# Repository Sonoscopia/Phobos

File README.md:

# PHOBOS
Code and instructional content.
Homepage is [here](https://sonoscopia.pt/en/works/phobos/) 

## Description
Phobos is a set of small robots and automatic music generation devices that form a Dysfunctional Robotic Orchestra, an orchestra with strange instruments with defects, genetic mutations and erratic behaviors.

Phobos represents a critique of the technological overlapping over human thought, the function of labor and modern forms of slavery, as well as an historical retrospective of the various attempts of human liberation through machines, its technological utopias, the advances and retreats of freedoms. Its name comes from Greek mythology, where Phobos is the incarnation of fear, and is also the name of the largest moon of Mars, doomed to disappear due to the proximity of its orbit to the planet. 

## Credits
- Conception and artistic direction: Gustavo Costa 
- New instruments by: Henrique Fernandes, Gustavo Costa, Alberto Lopes
- Guest musicians and instrument builders: Thierry Madiot, Vincent Martial and Hanna Hartman
- Programming and robotics: Tiago Ângelo and João Menezes
- Composition: Carlos Guedes, Rui Dias and José Alberto Gomes
- Cenography: Igor Gandra (Teatro de Ferro)
- Video: Miguel C. Tavares
- Executive production: Patrícia Caveiro
- Production: Sonoscopia
- Technical assistance: Digitópia
- Logistic support: Teatro de Ferro
- Project funded by Republica Portuguesa / Cultura and DGArtes
- Partners: GNRation, NYU Abu Dhabi, CCVF, Centro Cultural de Ílhavo and Festival Bons Sons

## LICENSE
[![CC BY-NC 4.0][cc-by-nc-shield]][cc-by-nc]

This work is licensed under a
[Creative Commons Attribution-NonCommercial 4.0 International License][cc-by-nc].

[![CC BY-NC 4.0][cc-by-nc-image]][cc-by-nc]

[cc-by-nc]: https://creativecommons.org/licenses/by-nc/4.0/
[cc-by-nc-image]: https://licensebuttons.net/l/by-nc/4.0/88x31.png
[cc-by-nc-shield]: https://img.shields.io/badge/License-CC%20BY--NC%204.0-lightgrey.svg

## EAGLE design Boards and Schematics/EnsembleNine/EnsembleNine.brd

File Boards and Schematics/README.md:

# IMPORTANT NOTICE
These boards were designed to be etched and drilled by CNC at FEUP (Faculty of Engineering - University of Porto) in 2015. 

The boards might need some revision for modern print (ex: JLCPCB or PCBWAY)!!

If you want to make one for yourself I would advise making EnsembleTwo (check schematics to see which one better fits your needs...)

The Ensemble boards used RJ45 connectors, packing 4 signals in one cable. To use independent outputs the InstrumentHubs have a RJ45 input connector and separate output DC (5.5x2.1mm) connectors.

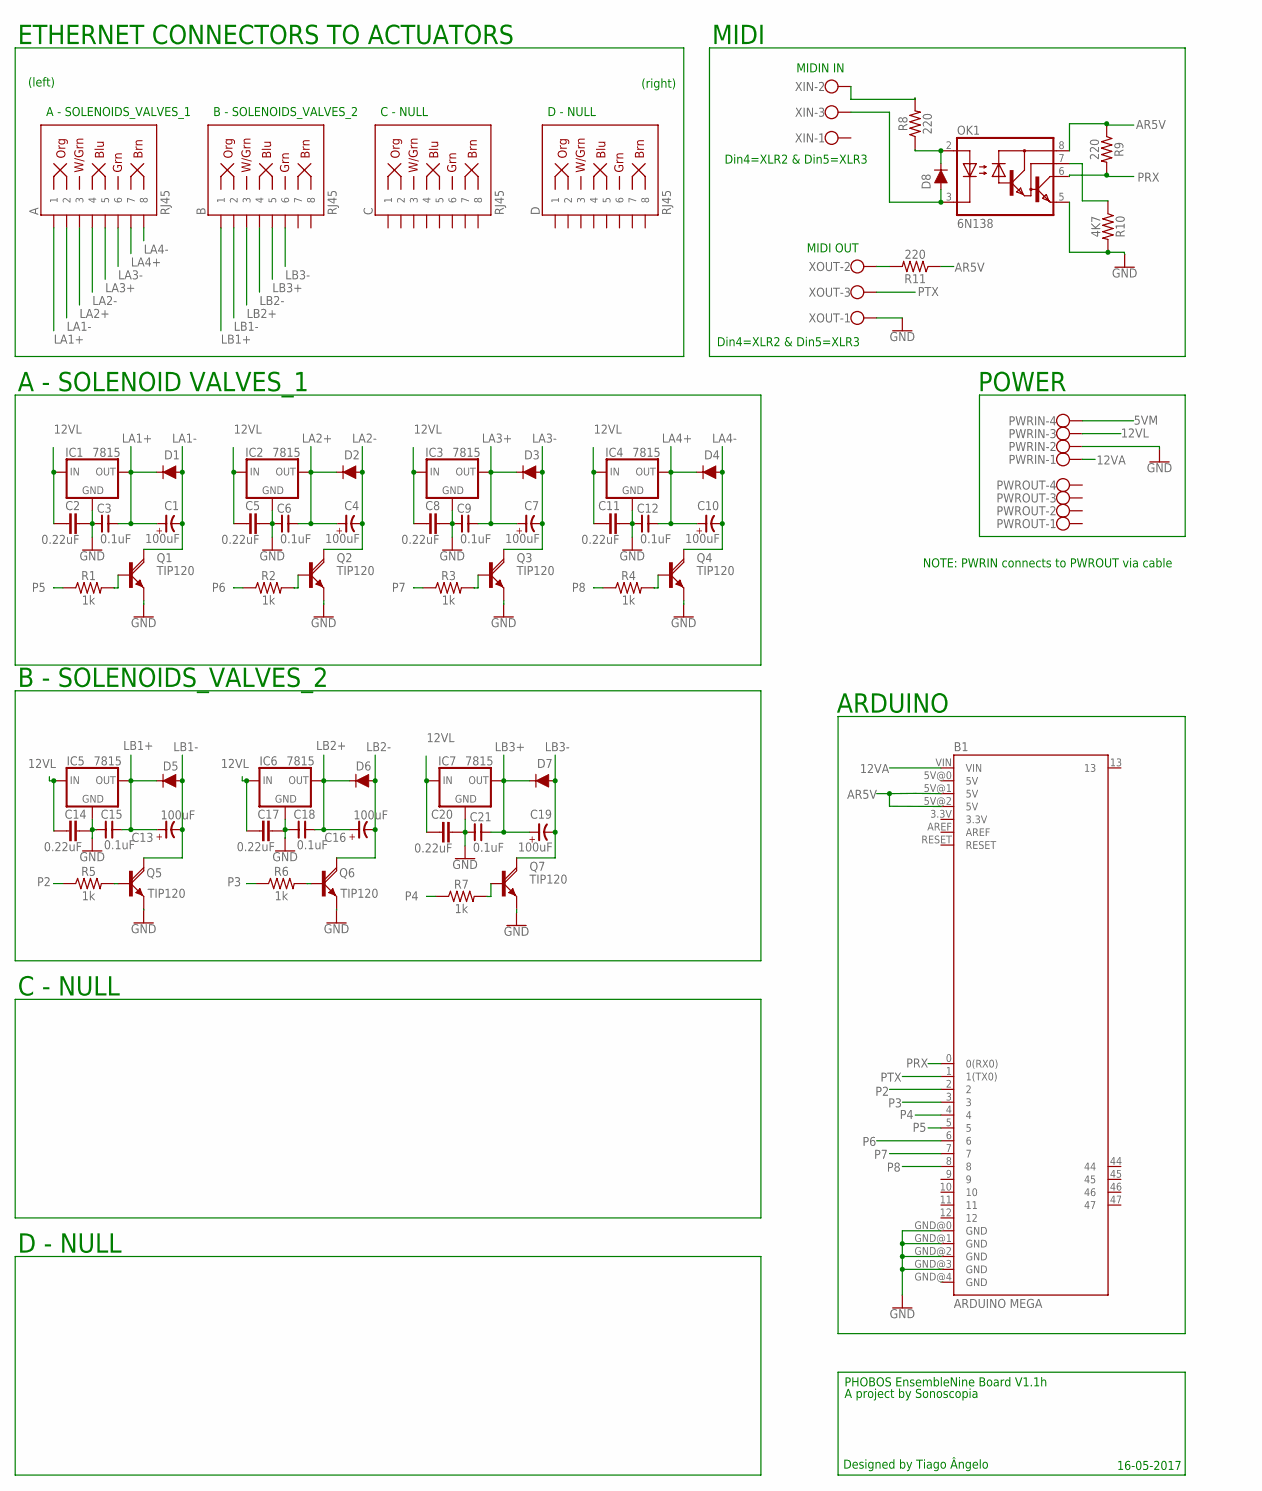
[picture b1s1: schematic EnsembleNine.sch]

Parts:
A: RJ45; RJ45-8
B: RJ45; RJ45-8
B1: ARDUINO MEGA; ARDUINO_MEGA
C: RJ45; RJ45-8
C1, C4, C7, C10, C19: 100uF; CAP-MASTER_E-020X050
C2, C5, C8, C11, C14, C17, C20: 0.22uF; C5B3
C3, C6, C9, C12, C15, C18, C21: 0.1uF; C025-050X025
C13, C16: 100uF; E-020X050
D: RJ45; RJ45-8
D1, D2, D3, D4, D5, D6, D7: 1A/50V/1.1V; DIODE-1N4001-KIT
D8: 200mA/100V/1V; DIODE-1N4148
IC1, IC2, IC3, IC4, IC5, IC6, IC7: 7815; 78XXS
OK1: 6N138; DIL08
PWRIN: W237-4
PWROUT: W237-4
Q1, Q2, Q3, Q4, Q7: TIP120; ROCKETFARM_TO220AV
Q5, Q6: TIP120; TO220AV
R1, R2, R3, R4, R5, R6, R7: 1k; AXIAL-0.1
R8, R9, R11: 220; AXIAL-0.3
R10: 4K7; AXIAL-0.3
XIN: W237-103
XOUT: W237-103

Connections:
5VM: PWRIN.4
12VA: B1.VIN, PWRIN.1
12VL: C2.1, C5.1, C8.1, C11.1, C14.1, C17.1, C20.1, IC1.IN, IC2.IN, IC3.IN, IC4.IN, IC5.IN, IC6.IN, IC7.IN, PWRIN.3
AR5V: B1.5V@1 (5V), B1.5V@2 (5V), OK1.8 (VCC), R9.P$1 (1), R11.P$1 (1)
GND: B1.GND@0 (GND), B1.GND@1 (GND), B1.GND@2 (GND), B1.GND@3 (GND), C2.2, C3.1, C5.2, C6.1, C8.2, C9.1, C11.2, C12.1, C14.2, C15.1, C17.2, C18.1, C20.2, C21.1, IC1.GND, IC2.GND, IC3.GND, IC4.GND, IC5.GND, IC6.GND, IC7.GND, OK1.5 (GND), PWRIN.2, Q1.E, Q2.E, Q3.E, Q4.E, Q5.E, Q6.E, Q7.E, R10.P$2 (2), XOUT.1
LA1+: A.1, C1.+, C3.2, D1.C, IC1.OUT
LA1-: A.2, C1.-, D1.A, Q1.C
LA2+: A.3, C4.+, C6.2, D2.C, IC2.OUT
LA2-: A.4, C4.-, D2.A, Q2.C
LA3+: A.5, C7.+, C9.2, D3.C, IC3.OUT
LA3-: A.6, C7.-, D3.A, Q3.C
LA4+: A.7, C10.+, C12.2, D4.C, IC4.OUT
LA4-: A.8, C10.-, D4.A, Q4.C
LB1+: B.1, C13.+, C15.2, D5.C, IC5.OUT
LB1-: B.2, C13.-, D5.A, Q5.C
LB2+: B.3, C16.+, C18.2, D6.C, IC6.OUT
LB2-: B.4, C16.-, D6.A, Q6.C
LB3+: B.5, C19.+, C21.2, D7.C, IC7.OUT
LB3-: B.6, C19.-, D7.A, Q7.C
unnamed: Q3.B, R3.P$2 (2)
unnamed: R11.P$2 (2), XOUT.2
unnamed: Q4.B, R4.P$2 (2)
unnamed: Q6.B, R6.P$2 (2)
unnamed: Q5.B, R5.P$2 (2)
unnamed: Q7.B, R7.P$2 (2)
unnamed: Q1.B, R1.P$2 (2)
unnamed: Q2.B, R2.P$2 (2)
unnamed: D8.A, OK1.3 (C), XIN.3
unnamed: D8.C, OK1.2 (A), R8.P$1 (1)
unnamed: R8.P$2 (2), XIN.2
unnamed: OK1.7 (VB), R10.P$1 (1)
P2: B1.2, R5.P$1 (1)
P3: B1.3, R6.P$1 (1)
P4: B1.4, R7.P$1 (1)
P5: B1.5, R1.P$1 (1)
P6: B1.6, R2.P$1 (1)
P7: B1.7, R3.P$1 (1)
P8: B1.8, R4.P$1 (1)
PRX: B1.0 (0(RX0)), OK1.6 (VO), R9.P$2 (2)
PTX: B1.1 (1(TX0)), XOUT.3

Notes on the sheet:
Din4=XLR2 & Din5=XLR3
MIDI OUT
MIDIN IN
POWER
MIDI
ARDUINO
(right)
(left)
ETHERNET CONNECTORS TO ACTUATORS
D - NULL
C - NULL
B - SOLENOIDS_VALVES_2
A - SOLENOIDS_VALVES_1
A - SOLENOID VALVES_1
PHOBOS EnsembleNine Board V1.1h
Designed by Tiago Ângelo
A project by Sonoscopia
16-05-2017
NOTE: PWRIN connects to PWROUT via cable

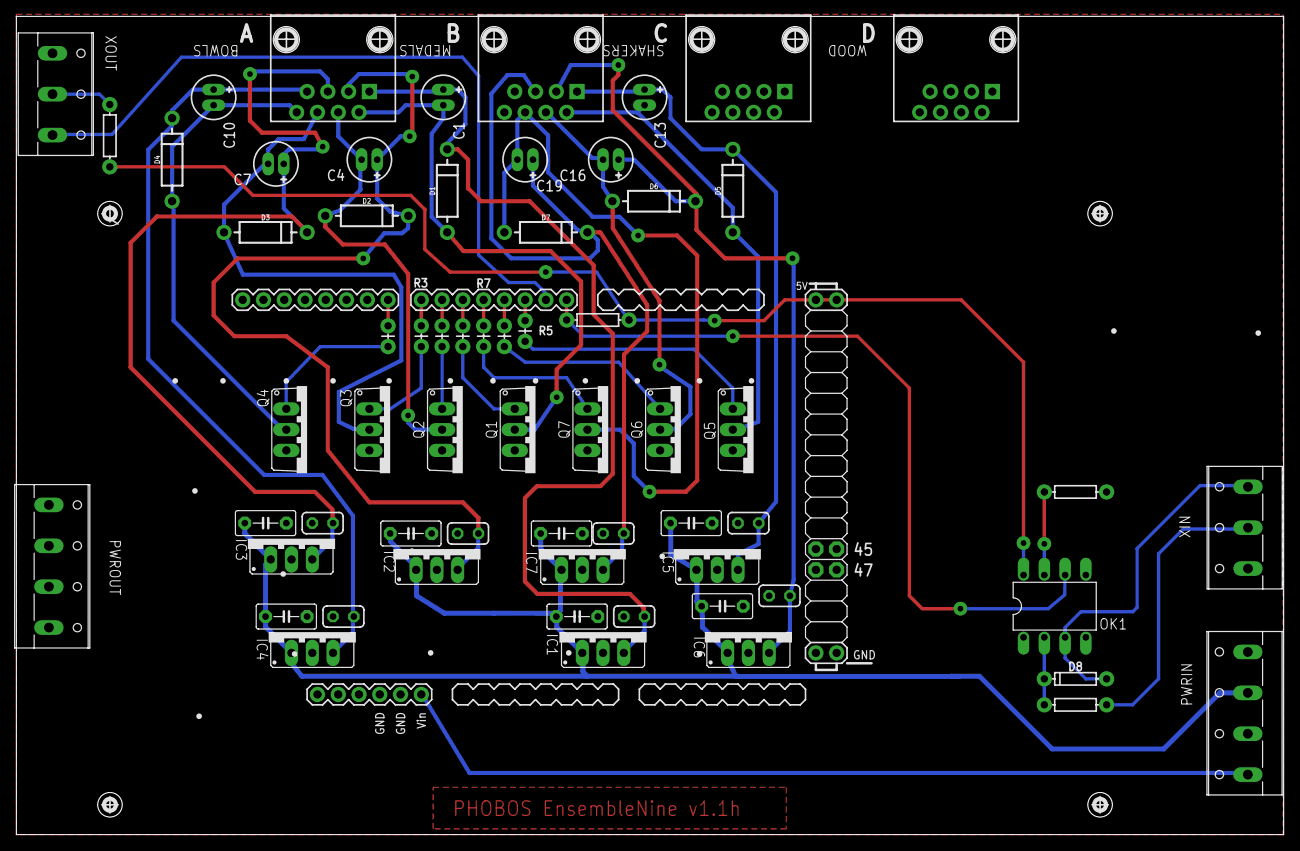
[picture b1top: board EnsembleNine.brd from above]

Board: 2 copper layers, 155.0 x 100.1 mm, 64 parts (0 on the bottom side), 39 nets.

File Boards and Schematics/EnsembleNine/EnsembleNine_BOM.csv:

Partlist exported from C:/Users/tiago/Documents/eagle/PHOBOS/EnsembleNine/EnsembleNine.sch at 16-05-2017 04:48

Qty Value         Device                  Package              Parts                             Description               MF                MPN     OC_FARNELL OC_NEWARK PROD_ID    SF_ID     VALUE        
2                 W237-103                W237-103             XIN, XOUT                         WAGO SCREW CLAMP                            237-103 unknown    18M7116                                     
2                 W237-4                  W237-4               PWRIN, PWROUT                     WAGO SCREW CLAMP                                    unknown    unknown                                     
7   0.1uF         CNP-C025-050X025        C025-050X025         C3, C6, C9, C12, C15, C18, C21    NON-POLARIZED CAP                                                                                          
7   0.22uF        C5/3                    C5B3                 C2, C5, C8, C11, C14, C17, C20    CAPACITOR                                                                                                  
5   100uF         CAP-MASTER_CP-E-020X050 CAP-MASTER_E-020X050 C1, C4, C7, C10, C19              POLARIZED CAP                                                                                              
2   100uF         CP-E-020X050            E-020X050            C13, C16                          POLARIZED CAP                                                                                              
7   1A/50V/1.1V   DIODE-KIT2              DIODE-1N4001-KIT     D1, D2, D3, D4, D5, D6, D7        Diode                                                                    DIO-09176            1A/50V/1.1V  
7   1k            1KOHM-VERT-1/4W-1%      AXIAL-0.1            R1, R2, R3, R4, R5, R6, R7        1kO resistor                                                             RES-12182            1k           
1   200mA/100V/1V DIODE-1N4148            DIODE-1N4148         D8                                Diode                                                                    DIO-08378            200mA/100V/1V
3   220           1KOHM-HORIZ-1/4W-5%     AXIAL-0.3            R8, R9, R11                       1kO resistor                                                             RES-08380            1k           
1   4K7           1KOHM-HORIZ-1/4W-5%     AXIAL-0.3            R10                               1kO resistor                                                             RES-08380            1k           
1   6N138         6N138                   DIL08                OK1                               MOTOROLA OPTO COUPLER     VISHAY/TELEFUNKEN 6N138   9860150    35K5294                                     
7   7815          78XXS                   78XXS                IC1, IC2, IC3, IC4, IC5, IC6, IC7 VOLTAGE REGULATOR                                                                                          
1   ARDUINO MEGA  ARDUINO_MEGA_R3FULL     ARDUINO_MEGA         B1                                Arduino Mega R3                                                                                            
4   RJ45          RJ45-8                  RJ45-8               A, B, C, D                        RJ45 Jack - 8 pin                                                        CONN-08506 PRT-00643 RJ45         
5   TIP120        ROCKETFARM_TIP120V      ROCKETFARM_TO220AV   Q1, Q2, Q3, Q4, Q7                NPN DARLINGTON TRANSISTOR                                                                                  
2   TIP120        TIP120V                 TO220AV              Q5, Q6                            NPN DARLINGTON TRANSISTOR

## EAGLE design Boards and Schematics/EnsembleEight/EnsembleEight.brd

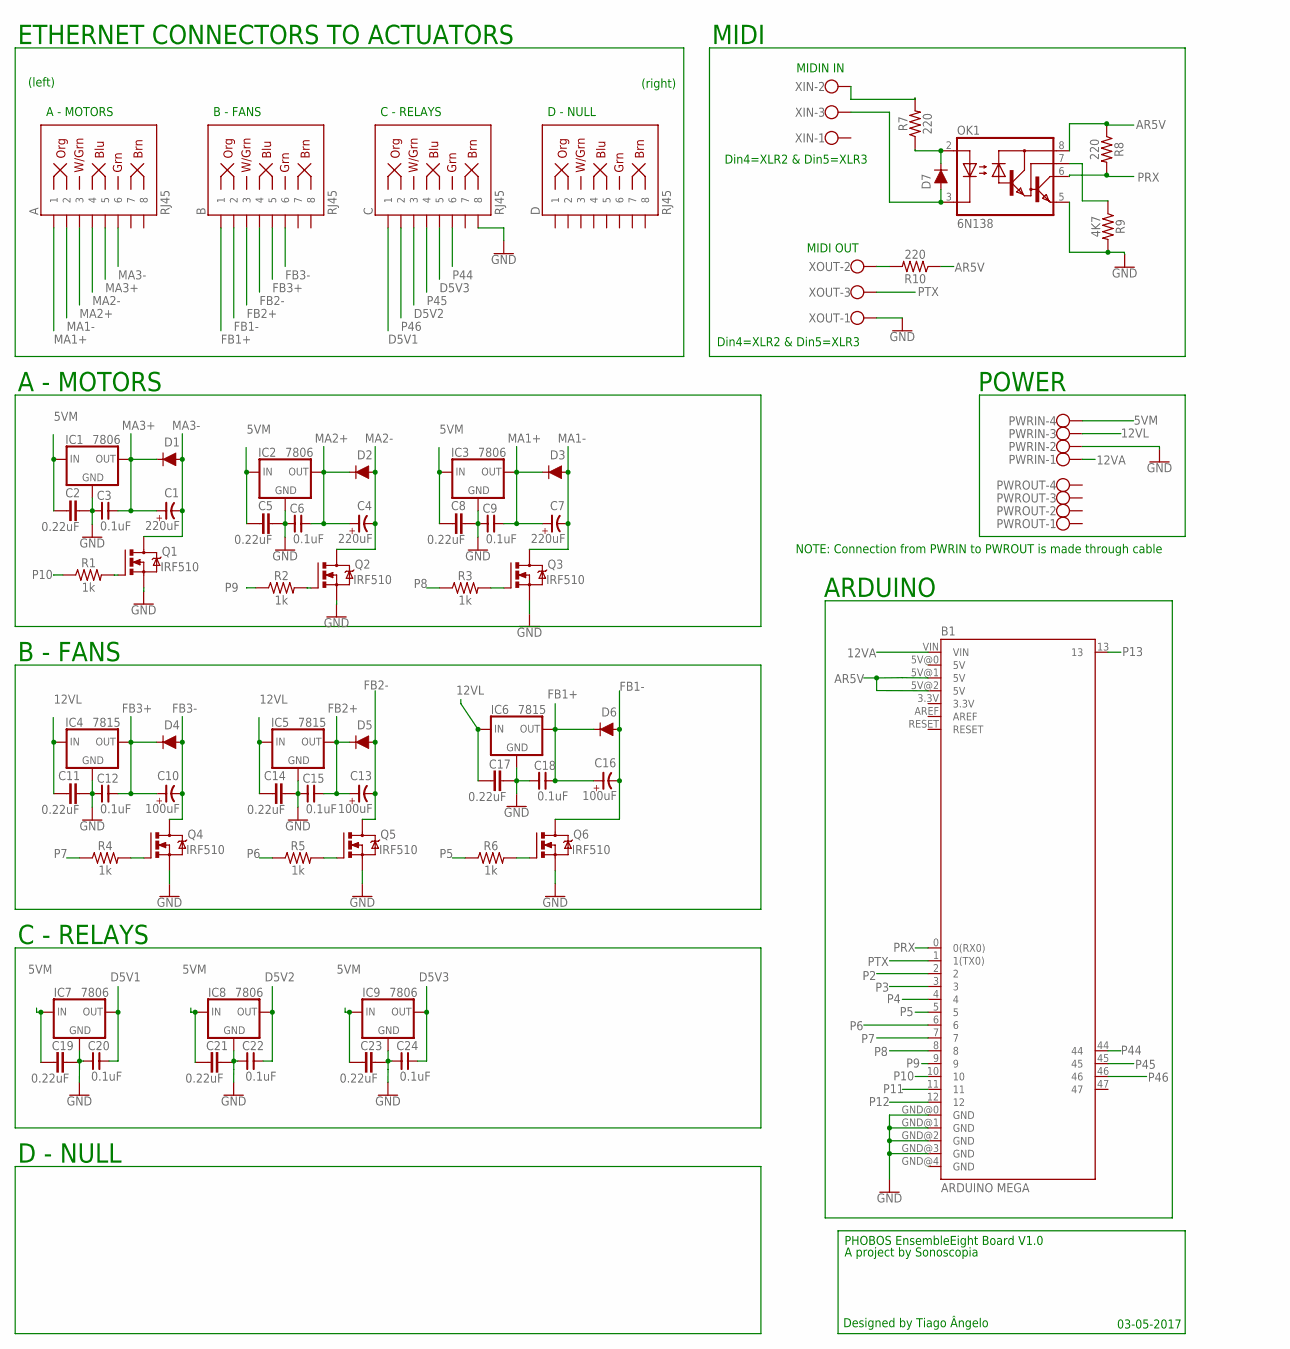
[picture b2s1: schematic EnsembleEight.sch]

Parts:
A: RJ45; RJ45-8
B: RJ45; RJ45-8
B1: ARDUINO MEGA; ARDUINO_MEGA
C: RJ45; RJ45-8
C1, C4, C7: 220uF; E-035X080
C2, C5, C8, C11, C14, C17, C19, C21, C23: 0.22uF; C5B3
C3, C6, C9, C12, C15, C18, C20, C22, C24: 0.1uF; C025-050X025
C10, C13, C16: 100uF; CAP-MASTER_E-020X050
D: RJ45; RJ45-8
D1, D2, D3, D4, D5, D6: 1A/50V/1.1V; DIODE-1N4001-KIT
D7: 200mA/100V/1V; DIODE-1N4148
IC1, IC2, IC3, IC7, IC8, IC9: 7806; 78XXS
IC4, IC5, IC6: 7815; 78XXS
OK1: 6N138; DIL08
PWRIN: W237-4
PWROUT: W237-4
Q1, Q2, Q3, Q4, Q5, Q6: IRF510; TO220BV
R1, R2, R3, R4, R5, R6: 1k; AXIAL-0.1
R7, R8, R10: 220; AXIAL-0.3
R9: 4K7; AXIAL-0.3
XIN: W237-103
XOUT: W237-103

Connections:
5VM: C2.1, C5.1, C8.1, C19.1, C21.1, C23.1, IC1.IN, IC2.IN, IC3.IN, IC7.IN, IC8.IN, IC9.IN, PWRIN.4
12VA: B1.VIN, PWRIN.1
12VL: C11.1, C14.1, C17.1, IC4.IN, IC5.IN, IC6.IN, PWRIN.3
AR5V: B1.5V@1 (5V), B1.5V@2 (5V), OK1.8 (VCC), R8.P$1 (1), R10.P$1 (1)
D5V1: C.1, C20.2, IC7.OUT
D5V2: C.3, C22.2, IC8.OUT
D5V3: C.5, C24.2, IC9.OUT
FB1+: B.1, C16.+, C18.2, D6.C, IC6.OUT
FB1-: B.2, C16.-, D6.A, Q6.D
FB2+: B.3, C13.+, C15.2, D5.C, IC5.OUT
FB2-: B.4, C13.-, D5.A, Q5.D
FB3+: B.5, C10.+, C12.2, D4.C, IC4.OUT
FB3-: B.6, C10.-, D4.A, Q4.D
GND: B1.GND@0 (GND), B1.GND@1 (GND), B1.GND@2 (GND), B1.GND@3 (GND), C.8, C2.2, C3.1, C5.2, C6.1, C8.2, C9.1, C11.2, C12.1, C14.2, C15.1, C17.2, C18.1, C19.2, C20.1, C21.2, C22.1, C23.2, C24.1, IC1.GND, IC2.GND, IC3.GND, IC4.GND, IC5.GND, IC6.GND, IC7.GND, IC8.GND, IC9.GND, OK1.5 (GND), PWRIN.2, Q1.S, Q2.S, Q3.S, Q4.S, Q5.S, Q6.S, R9.P$2 (2), XOUT.1
MA1+: A.1, C7.+, C9.2, D3.C, IC3.OUT
MA1-: A.2, C7.-, D3.A, Q3.D
MA2+: A.3, C4.+, C6.2, D2.C, IC2.OUT
MA2-: A.4, C4.-, D2.A, Q2.D
MA3+: A.5, C1.+, C3.2, D1.C, IC1.OUT
MA3-: A.6, C1.-, D1.A, Q1.D
unnamed: Q1.G, R1.P$2 (2)
unnamed: R10.P$2 (2), XOUT.2
unnamed: Q3.G, R3.P$2 (2)
unnamed: Q4.G, R4.P$2 (2)
unnamed: Q5.G, R5.P$2 (2)
unnamed: Q6.G, R6.P$2 (2)
unnamed: Q2.G, R2.P$2 (2)
unnamed: D7.A, OK1.3 (C), XIN.3
unnamed: D7.C, OK1.2 (A), R7.P$1 (1)
unnamed: R7.P$2 (2), XIN.2
unnamed: OK1.7 (VB), R9.P$1 (1)
P2: B1.2
P3: B1.3
P4: B1.4
P5: B1.5, R6.P$1 (1)
P6: B1.6, R5.P$1 (1)
P7: B1.7, R4.P$1 (1)
P8: B1.8, R3.P$1 (1)
P9: B1.9, R2.P$1 (1)
P10: B1.10, R1.P$1 (1)
P11: B1.11
P12: B1.12
P13: B1.13
P44: B1.44, C.6
P45: B1.45, C.4
P46: B1.46, C.2
PRX: B1.0 (0(RX0)), OK1.6 (VO), R8.P$2 (2)
PTX: B1.1 (1(TX0)), XOUT.3

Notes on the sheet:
Din4=XLR2 & Din5=XLR3
MIDI OUT
MIDIN IN
POWER
MIDI
ARDUINO
(right)
(left)
ETHERNET CONNECTORS TO ACTUATORS
D - NULL
C - RELAYS
B - FANS
A - MOTORS
PHOBOS EnsembleEight Board V1.0
Designed by Tiago Ângelo
A project by Sonoscopia
03-05-2017
NOTE: Connection from PWRIN to PWROUT is made through cable

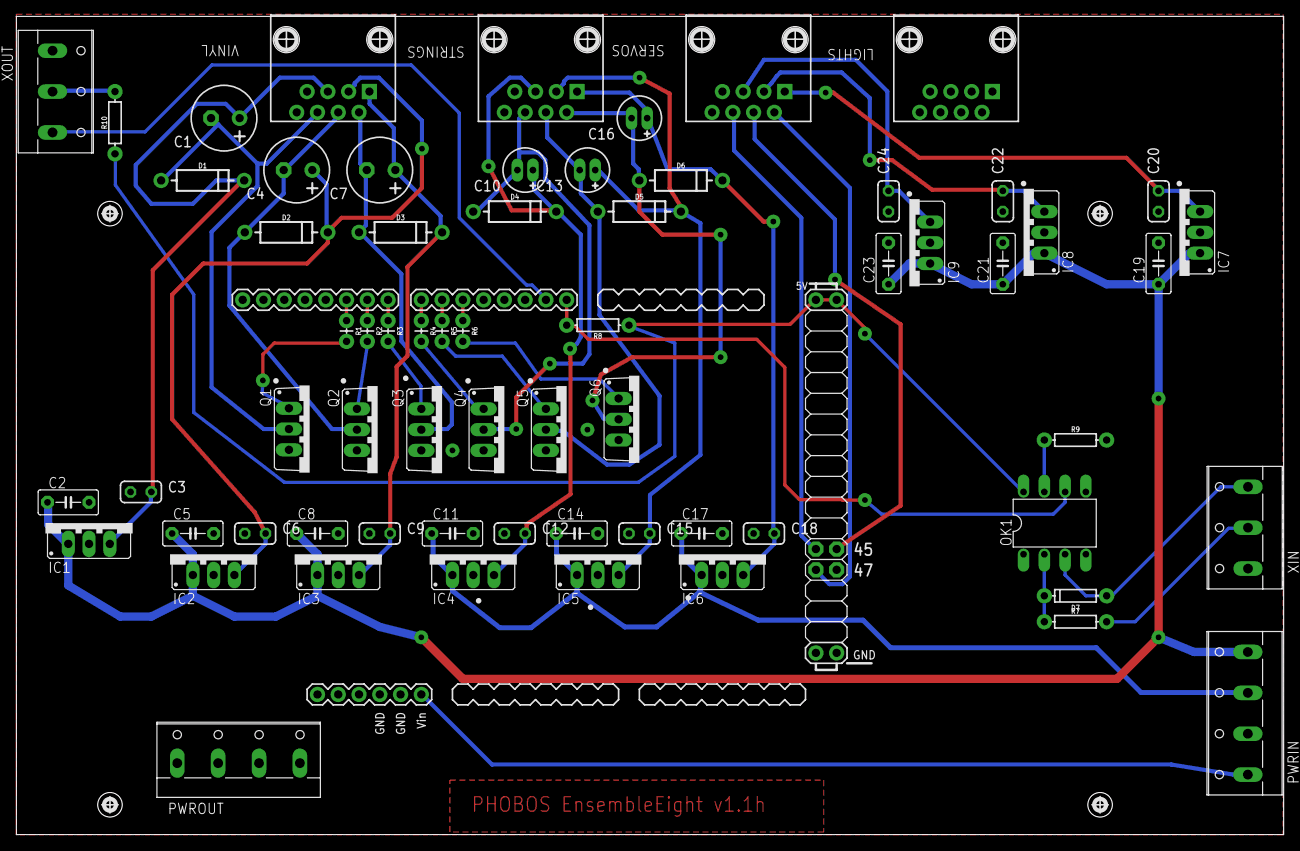
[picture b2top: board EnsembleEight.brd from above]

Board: 2 copper layers, 155.0 x 100.1 mm, 66 parts (0 on the bottom side), 42 nets.

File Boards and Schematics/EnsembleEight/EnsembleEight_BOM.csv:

Partlist exported from C:/Users/tiago/Documents/eagle/PHOBOS/EnsembleEight/EnsembleEight.sch at 05-05-2017 16:57

Qty Value         Device                  Package              Parts                                    Description           MF                MPN     OC_FARNELL OC_NEWARK PROD_ID    SF_ID     VALUE        
2                 W237-103                W237-103             XIN, XOUT                                WAGO SCREW CLAMP                        237-103 unknown    18M7116                                     
2                 W237-4                  W237-4               PWRIN, PWROUT                            WAGO SCREW CLAMP                                unknown    unknown                                     
9   0.1uF         CNP-C025-050X025        C025-050X025         C3, C6, C9, C12, C15, C18, C20, C22, C24 NON-POLARIZED CAP                                                                                      
9   0.22uF        C5/3                    C5B3                 C2, C5, C8, C11, C14, C17, C19, C21, C23 CAPACITOR                                                                                              
3   100uF         CAP-MASTER_CP-E-020X050 CAP-MASTER_E-020X050 C10, C13, C16                            POLARIZED CAP                                                                                          
6   1A/50V/1.1V   DIODE-KIT2              DIODE-1N4001-KIT     D1, D2, D3, D4, D5, D6                   Diode                                                                DIO-09176            1A/50V/1.1V  
6   1k            1KOHM-VERT-1/4W-1%      AXIAL-0.1            R1, R2, R3, R4, R5, R6                   1kO resistor                                                         RES-12182            1k           
1   200mA/100V/1V DIODE-1N4148            DIODE-1N4148         D7                                       Diode                                                                DIO-08378            200mA/100V/1V
3   220           1KOHM-HORIZ-1/4W-5%     AXIAL-0.3            R7, R8, R10                              1kO resistor                                                         RES-08380            1k           
3   220uF         CP-E-035X080            E-035X080            C1, C4, C7                               POLARIZED CAP                                                                                          
1   4K7           1KOHM-HORIZ-1/4W-5%     AXIAL-0.3            R9                                       1kO resistor                                                         RES-08380            1k           
1   6N138         6N138                   DIL08                OK1                                      MOTOROLA OPTO COUPLER VISHAY/TELEFUNKEN 6N138   9860150    35K5294                                     
6   7806          78XXS                   78XXS                IC1, IC2, IC3, IC7, IC8, IC9             VOLTAGE REGULATOR                                                                                      
3   7815          78XXS                   78XXS                IC4, IC5, IC6                            VOLTAGE REGULATOR                                                                                      
1   ARDUINO MEGA  ARDUINO_MEGA_R3FULL     ARDUINO_MEGA         B1                                       Arduino Mega R3                                                                                        
6   IRF510        IRF520                  TO220BV              Q1, Q2, Q3, Q4, Q5, Q6                   HEXFET Power MOSFET                                                                                    
4   RJ45          RJ45-8                  RJ45-8               A, B, C, D                               RJ45 Jack - 8 pin                                                    CONN-08506 PRT-00643 RJ45

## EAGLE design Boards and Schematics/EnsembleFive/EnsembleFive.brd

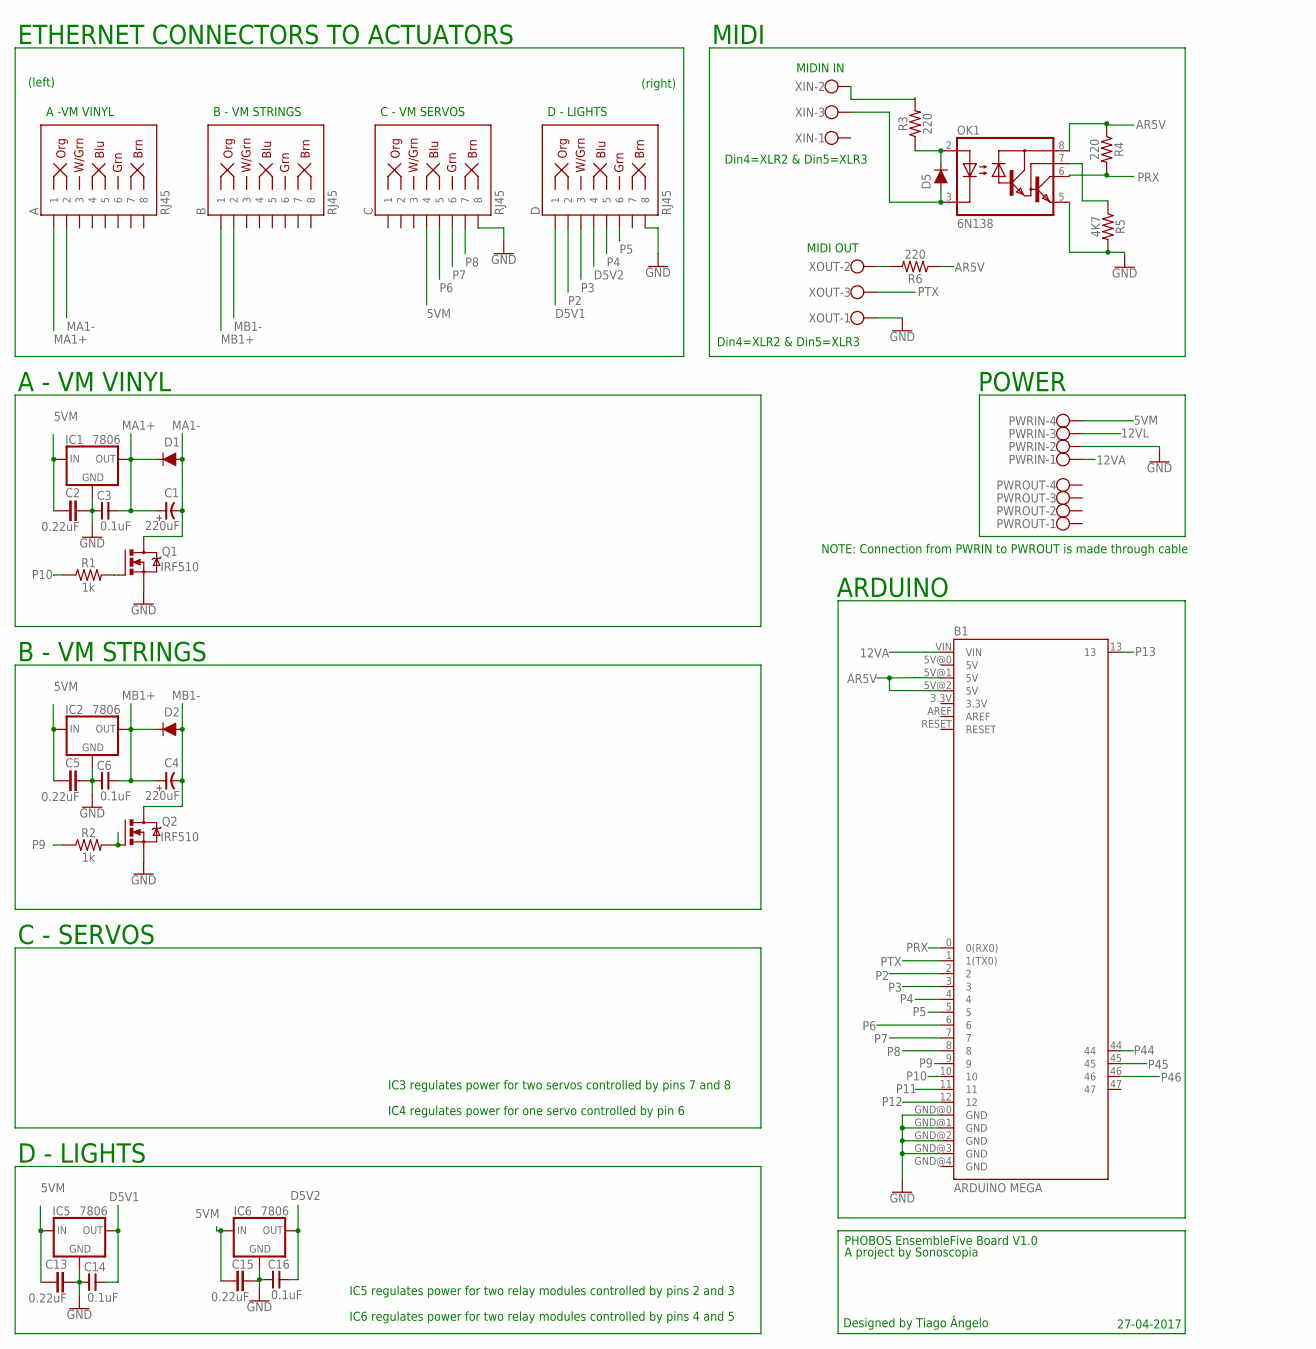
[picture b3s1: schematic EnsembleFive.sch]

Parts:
A: RJ45; RJ45-8
B: RJ45; RJ45-8
B1: ARDUINO MEGA; ARDUINO_MEGA
C: RJ45; RJ45-8
C1, C4: 220uF; E-035X080
C2, C5, C13, C15: 0.22uF; C5B3
C3, C6, C14, C16: 0.1uF; C025-050X025
D: RJ45; RJ45-8
D1, D2: 1A/50V/1.1V; DIODE-1N4001-KIT
D5: 200mA/100V/1V; DIODE-1N4148
IC1, IC2, IC5, IC6: 7806; 78XXS
OK1: 6N138; DIL08
PWRIN: W237-4
PWROUT: W237-4
Q1, Q2: IRF510; TO220BV
R1, R2: 1k; AXIAL-0.1
R3, R4, R6: 220; AXIAL-0.3
R5: 4K7; AXIAL-0.3
XIN: W237-103
XOUT: W237-103

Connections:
5VM: C.4, C2.1, C5.1, C13.1, C15.1, IC1.IN, IC2.IN, IC5.IN, IC6.IN, PWRIN.4
12VA: B1.VIN, PWRIN.1
12VL: PWRIN.3
AR5V: B1.5V@1 (5V), B1.5V@2 (5V), OK1.8 (VCC), R4.P$1 (1), R6.P$1 (1)
D5V1: C14.2, D.1, IC5.OUT
D5V2: C16.2, D.4, IC6.OUT
GND: B1.GND@0 (GND), B1.GND@1 (GND), B1.GND@2 (GND), B1.GND@3 (GND), C.8, C2.2, C3.1, C5.2, C6.1, C13.2, C14.1, C15.2, C16.1, D.8, IC1.GND, IC2.GND, IC5.GND, IC6.GND, OK1.5 (GND), PWRIN.2, Q1.S, Q2.S, R5.P$2 (2), XOUT.1
MA1+: A.1, C1.+, C3.2, D1.C, IC1.OUT
MA1-: A.2, C1.-, D1.A, Q1.D
MB1+: B.1, C4.+, C6.2, D2.C, IC2.OUT
MB1-: B.2, C4.-, D2.A, Q2.D
unnamed: Q1.G, R1.P$2 (2)
unnamed: R6.P$2 (2), XOUT.2
unnamed: Q2.G, R2.P$2 (2)
unnamed: D5.A, OK1.3 (C), XIN.3
unnamed: D5.C, OK1.2 (A), R3.P$1 (1)
unnamed: R3.P$2 (2), XIN.2
unnamed: OK1.7 (VB), R5.P$1 (1)
P2: B1.2, D.2
P3: B1.3, D.3
P4: B1.4, D.5
P5: B1.5, D.6
P6: B1.6, C.5
P7: B1.7, C.6
P8: B1.8, C.7
P9: B1.9, R2.P$1 (1)
P10: B1.10, R1.P$1 (1)
P11: B1.11
P12: B1.12
P13: B1.13
P44: B1.44
P45: B1.45
P46: B1.46
PRX: B1.0 (0(RX0)), OK1.6 (VO), R4.P$2 (2)
PTX: B1.1 (1(TX0)), XOUT.3

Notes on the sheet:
Din4=XLR2 & Din5=XLR3
MIDI OUT
MIDIN IN
POWER
MIDI
ARDUINO
(right)
(left)
ETHERNET CONNECTORS TO ACTUATORS
D - LIGHTS
C - VM SERVOS
B - VM STRINGS
A -VM VINYL
A - VM VINYL
C - SERVOS
PHOBOS EnsembleFive Board V1.0
Designed by Tiago Ângelo
A project by Sonoscopia
27-04-2017
IC3 regulates power for two servos controlled by pins 7 and 8
IC4 regulates power for one servo controlled by pin 6
IC5 regulates power for two relay modules controlled by pins 2 and 3
IC6 regulates power for two relay modules controlled by pins 4 and 5
NOTE: Connection from PWRIN to PWROUT is made through cable

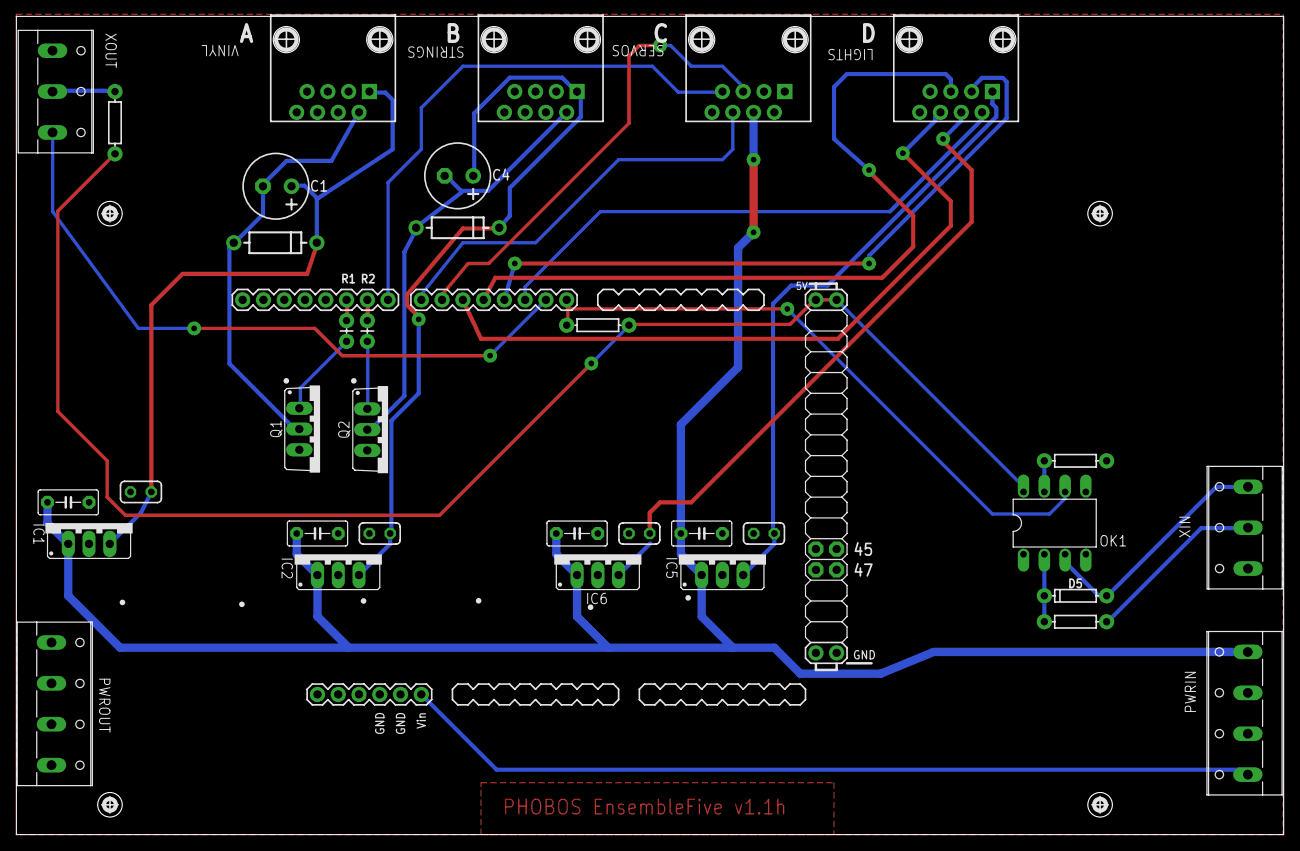
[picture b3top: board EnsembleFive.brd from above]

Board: 2 copper layers, 155.0 x 100.1 mm, 35 parts (0 on the bottom side), 28 nets.

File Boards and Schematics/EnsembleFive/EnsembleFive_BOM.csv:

Partlist exported from C:/Users/tiago/Documents/eagle/PHOBOS/EnsembleFive/EnsembleFive.sch at 15-05-2017 21:25

Qty Value         Device              Package          Parts              Description           MF                MPN     OC_FARNELL OC_NEWARK PROD_ID    SF_ID     VALUE        
2                 W237-103            W237-103         XIN, XOUT          WAGO SCREW CLAMP                        237-103 unknown    18M7116                                     
2                 W237-4              W237-4           PWRIN, PWROUT      WAGO SCREW CLAMP                                unknown    unknown                                     
4   0.1uF         CNP-C025-050X025    C025-050X025     C3, C6, C14, C16   NON-POLARIZED CAP                                                                                      
4   0.22uF        C5/3                C5B3             C2, C5, C13, C15   CAPACITOR                                                                                              
2   1A/50V/1.1V   DIODE-KIT2          DIODE-1N4001-KIT D1, D2             Diode                                                                DIO-09176            1A/50V/1.1V  
2   1k            1KOHM-VERT-1/4W-1%  AXIAL-0.1        R1, R2             1kO resistor                                                         RES-12182            1k           
1   200mA/100V/1V DIODE-1N4148        DIODE-1N4148     D5                 Diode                                                                DIO-08378            200mA/100V/1V
3   220           1KOHM-HORIZ-1/4W-5% AXIAL-0.3        R3, R4, R6         1kO resistor                                                         RES-08380            1k           
2   220uF         CP-E-035X080        E-035X080        C1, C4             POLARIZED CAP                                                                                          
1   4K7           1KOHM-HORIZ-1/4W-5% AXIAL-0.3        R5                 1kO resistor                                                         RES-08380            1k           
1   6N138         6N138               DIL08            OK1                MOTOROLA OPTO COUPLER VISHAY/TELEFUNKEN 6N138   9860150    35K5294                                     
4   7806          78XXS               78XXS            IC1, IC2, IC5, IC6 VOLTAGE REGULATOR                                                                                      
1   ARDUINO MEGA  ARDUINO_MEGA_R3FULL ARDUINO_MEGA     B1                 Arduino Mega R3                                                                                        
2   IRF510        IRF520              TO220BV          Q1, Q2             HEXFET Power MOSFET                                                                                    
4   RJ45          RJ45-8              RJ45-8           A, B, C, D         RJ45 Jack - 8 pin                                                    CONN-08506 PRT-00643 RJ45

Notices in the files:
parts and their libraries:
SparkFun-Connectors: Licensing: Creative Commons ShareAlike 4.0 International - https://creativecommons.org/licenses/by-sa/4.0
